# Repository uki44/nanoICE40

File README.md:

# nanoICE40
custom fpga development board using the ice40 fpga from lattice

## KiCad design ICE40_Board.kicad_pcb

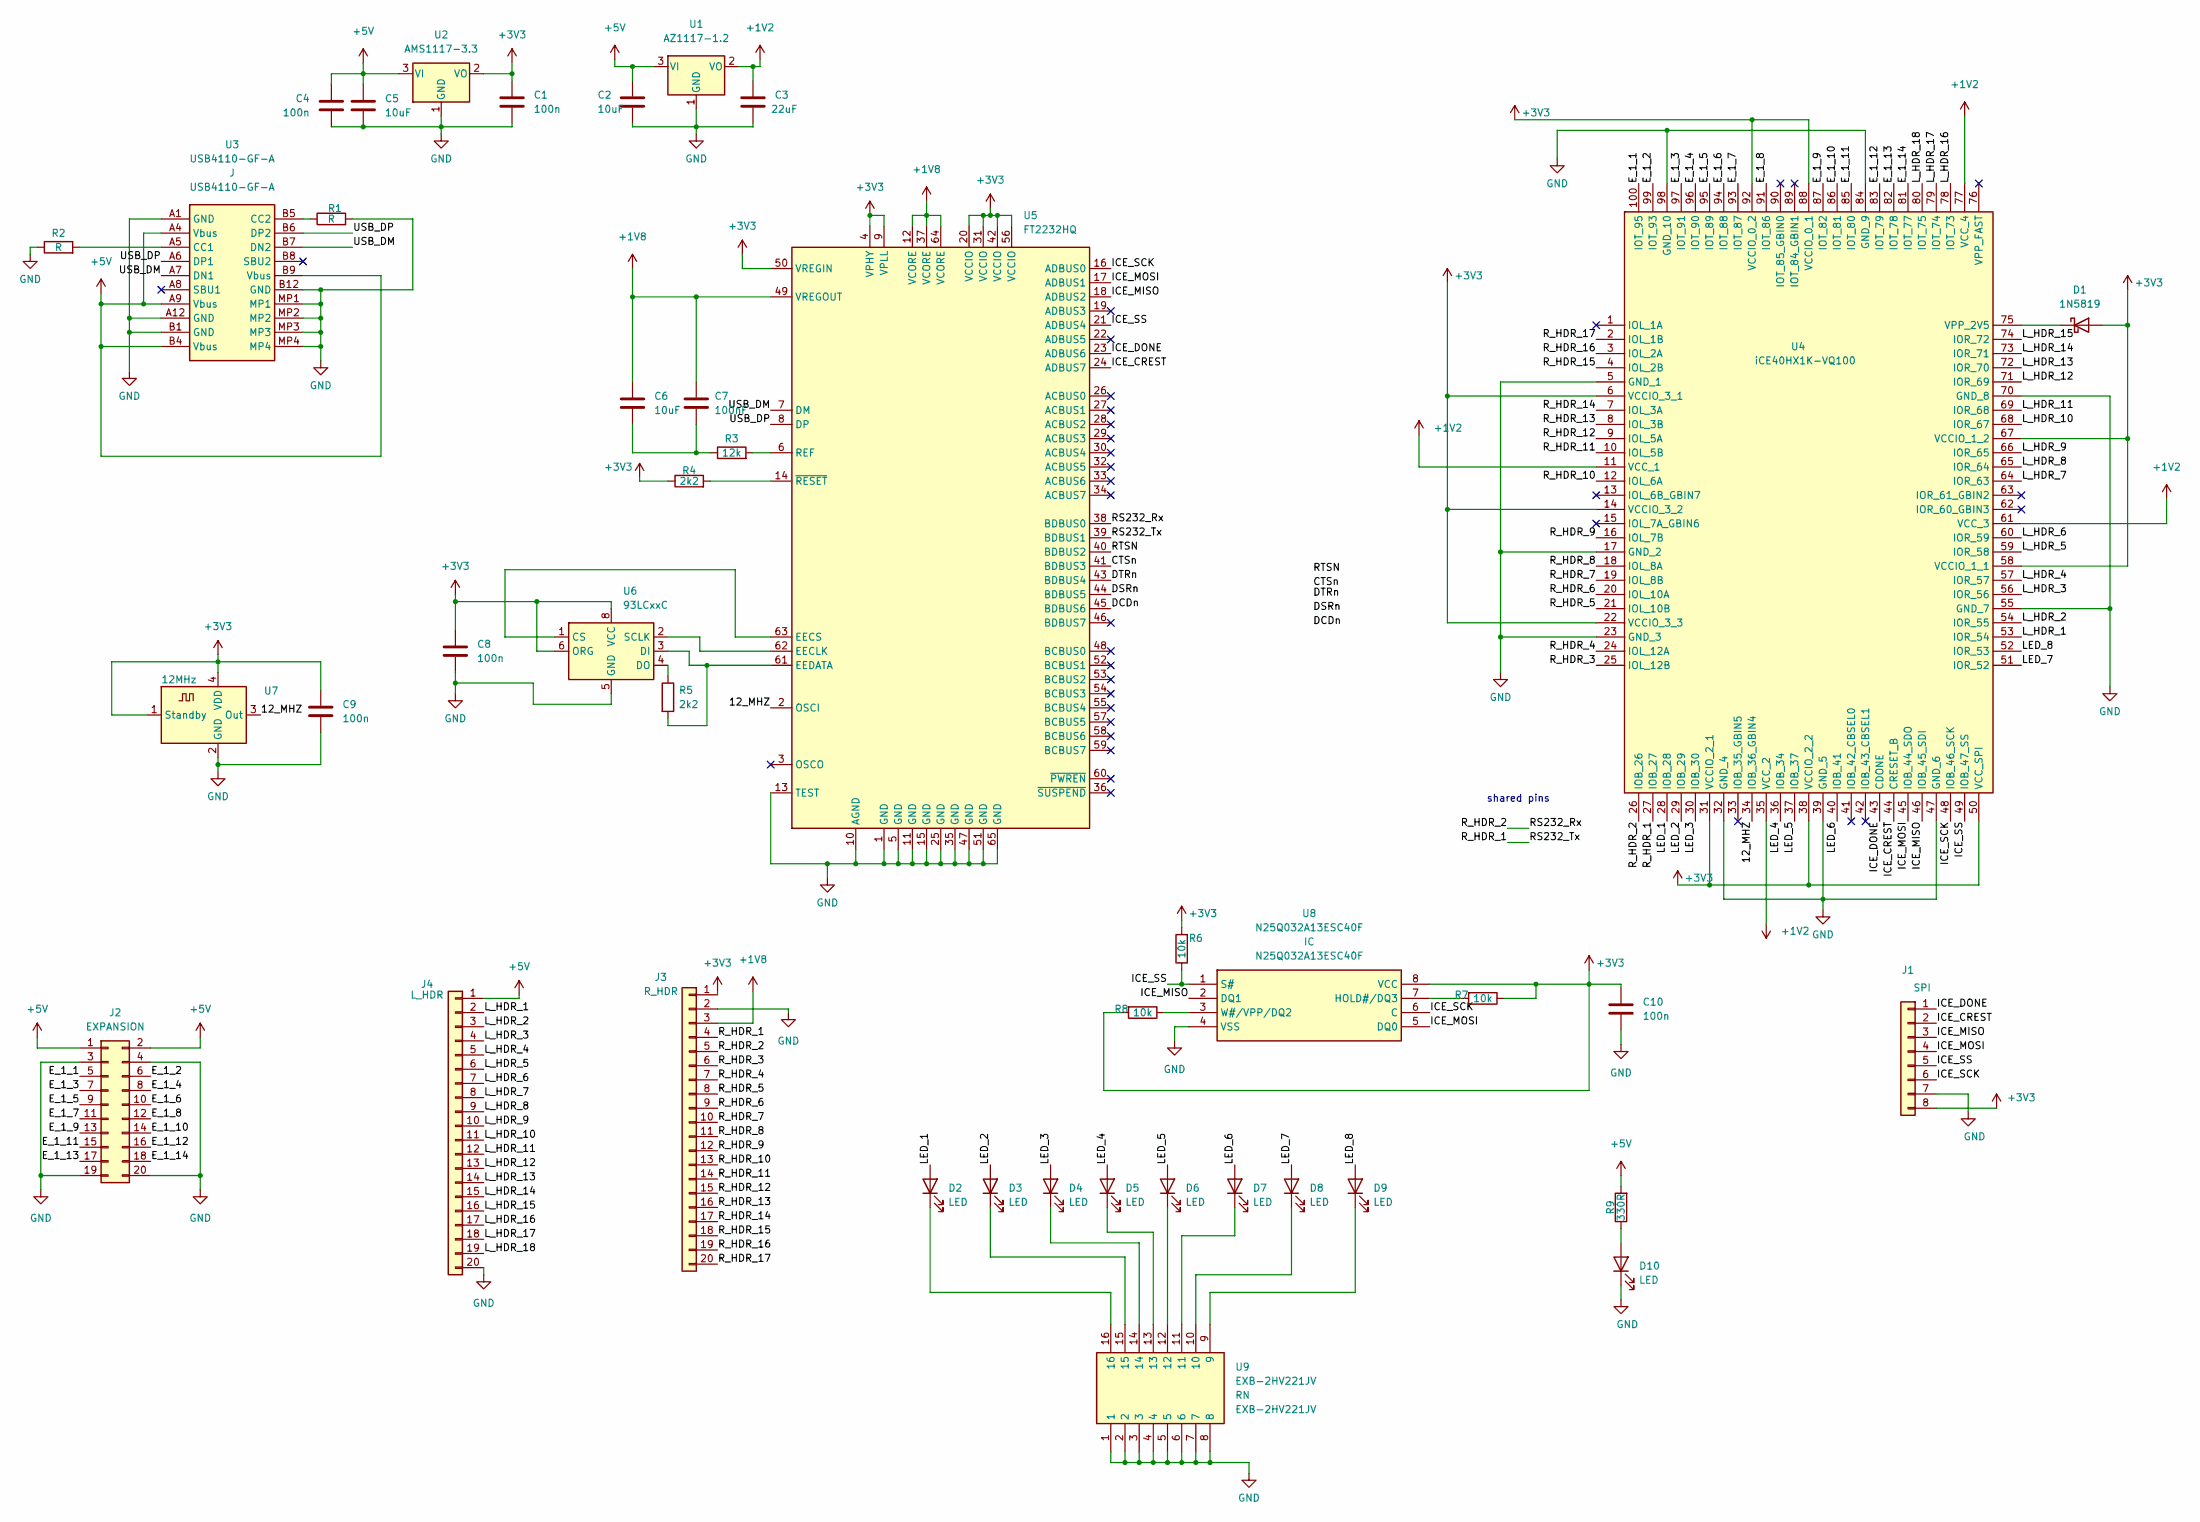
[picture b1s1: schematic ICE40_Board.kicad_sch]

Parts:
C1, C4, C8, C9, C10: 100n; C_0603_1608Metric
C2, C5, C6: 10uF; C_0603_1608Metric
C3: 22uF; C_0603_1608Metric
C7: 100nF; C_0603_1608Metric
D1: 1N5819; D_SOD-123
D2, D3, D4, D5, D6, D7, D8, D9, D10: LED; LED_0603_1608Metric
J1: SPI; PinHeader_1x08_P1.27mm_Vertical
J2: EXPANSION; PinHeader_2x10_P2.54mm_Vertical
J3: R_HDR; PinHeader_1x20_P2.54mm_Vertical
J4: L_HDR; PinHeader_1x20_P2.54mm_Vertical
R1, R2: R; R_0603_1608Metric
R3: 12k; R_0603_1608Metric
R4, R5: 2k2; R_0603_1608Metric
R6, R7, R8: 10k; R_0603_1608Metric
R9: 330R; R_0603_1608Metric
U1: AZ1117-1.2; SOT-223
U2: AMS1117-3.3; SOT-223
U3: USB4110-GF-A; USB4110GFA; Mouser Part Number 640-USB4110-GF-A
U4: iCE40HX1K-VQ100; QFP50P1600X1600X120-100N; Mouser Part Number 842-ICE40HX1K-VQ100
U5: FT2232HQ; QFN-64-1EP_9x9mm_P0.5mm_EP4.35x4.35mm
U6: 93LCxxC; SOIC127P600X175-8N
U7: 12MHz; Oscillator_SMD_Abracon_ASDMB-4Pin_2.5x2.0mm
U8: N25Q032A13ESC40F; SOIC127P600X175-8N; Mouser Part Number 913-N25Q032A13ESC40F
U9: EXB-2HV221JV; EXB2HV221JV; Mouser Part Number 667-EXB-2HV221JV

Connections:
+1V2: C3.1, U1.2 (VO), U4.11 (VCC_1), U4.35 (VCC_2), U4.61 (VCC_3), U4.77 (VCC_4)
+1V8: C6.1, C7.1, J3.3, U5.12 (VCORE), U5.37 (VCORE), U5.49 (VREGOUT), U5.64 (VCORE)
+3V3: C1.1, C8.1, C9.1, C10.1, D1.2 (A), J1.8, J3.1, R4.1, R6.2, R7.1, R8.2, U2.2 (VO), U4.6 (VCCIO_3_1), U4.14 (VCCIO_3_2), U4.22 (VCCIO_3_3), U4.31 (VCCIO_2_1), U4.38 (VCCIO_2_2), U4.50 (VCC_SPI), U4.58 (VCCIO_1_1), U4.67 (VCCIO_1_2), U4.88 (VCCIO_0_1), U4.92 (VCCIO_0_2), U5.4 (VPHY), U5.9 (VPLL), U5.20 (VCCIO), U5.31 (VCCIO), U5.42 (VCCIO), U5.50 (VREGIN), U5.56 (VCCIO), U6.6 (ORG), U6.8 (VCC), U7.1 (Standby), U7.4 (VDD), U8.8 (VCC)
+5V: C2.1, C4.2, C5.1, J2.1, J2.2, J4.1, R9.2, U1.3 (VI), U2.3 (VI), U3.A4 (Vbus), U3.A9 (Vbus), U3.B4 (Vbus), U3.B9 (Vbus)
/12_MHZ: U4.34 (IOB_36_GBIN4), U5.2 (OSCI), U7.3 (Out)
/CTSn: U5.41 (BDBUS3)
/DCDn: U5.45 (BDBUS6)
/DSRn: U5.44 (BDBUS5)
/DTRn: U5.43 (BDBUS4)
/E_1_1: J2.5, U4.100 (IOT_95)
/E_1_2: J2.6, U4.99 (IOT_93)
/E_1_3: J2.7, U4.97 (IOT_91)
/E_1_4: J2.8, U4.96 (IOT_90)
/E_1_5: J2.9, U4.95 (IOT_89)
/E_1_6: J2.10, U4.94 (IOT_88)
/E_1_7: J2.11, U4.93 (IOT_87)
/E_1_8: J2.12, U4.91 (IOT_86)
/E_1_9: J2.13, U4.87 (IOT_82)
/E_1_10: J2.14, U4.86 (IOT_81)
/E_1_11: J2.15, U4.85 (IOT_80)
/E_1_12: J2.16, U4.83 (IOT_79)
/E_1_13: J2.17, U4.82 (IOT_78)
/E_1_14: J2.18, U4.81 (IOT_77)
/ICE_CREST: J1.2, U4.44 (CRESET_B), U5.24 (ADBUS7)
/ICE_DONE: J1.1, U4.43 (CDONE), U5.23 (ADBUS6)
/ICE_MISO: J1.3, U4.46 (IOB_45_SDI), U5.18 (ADBUS2), U8.2 (DQ1)
/ICE_MOSI: J1.4, U4.45 (IOB_44_SDO), U5.17 (ADBUS1), U8.5 (DQ0)
/ICE_SCK: J1.6, U4.48 (IOB_46_SCK), U5.16 (ADBUS0), U8.6 (C)
/ICE_SS: J1.5, R6.1, U4.49 (IOB_47_SS), U5.21 (ADBUS4), U8.1 (S#)
/LED_1: D2.2 (A), U4.28 (IOB_28)
/LED_2: D3.2 (A), U4.29 (IOB_29)
/LED_3: D4.2 (A), U4.30 (IOB_30)
/LED_4: D5.2 (A), U4.36 (IOB_34)
/LED_5: D6.2 (A), U4.37 (IOB_37)
/LED_6: D7.2 (A), U4.40 (IOB_41)
/LED_7: D8.2 (A), U4.51 (IOR_52)
/LED_8: D9.2 (A), U4.52 (IOR_53)
/L_HDR_1: J4.2, U4.53 (IOR_54)
/L_HDR_2: J4.3, U4.54 (IOR_55)
/L_HDR_3: J4.4, U4.56 (IOR_56)
/L_HDR_4: J4.5, U4.57 (IOR_57)
/L_HDR_5: J4.6, U4.59 (IOR_58)
/L_HDR_6: J4.7, U4.60 (IOR_59)
/L_HDR_7: J4.8, U4.64 (IOR_63)
/L_HDR_8: J4.9, U4.65 (IOR_64)
/L_HDR_9: J4.10, U4.66 (IOR_65)
/L_HDR_10: J4.11, U4.68 (IOR_67)
/L_HDR_11: J4.12, U4.69 (IOR_68)
/L_HDR_12: J4.13, U4.71 (IOR_69)
/L_HDR_13: J4.14, U4.72 (IOR_70)
/L_HDR_14: J4.15, U4.73 (IOR_71)
/L_HDR_15: J4.16, U4.74 (IOR_72)
/L_HDR_16: J4.17, U4.78 (IOT_73)
/L_HDR_17: J4.18, U4.79 (IOT_74)
/L_HDR_18: J4.19, U4.80 (IOT_75)
/RS232_Rx: J3.5, U4.26 (IOB_26), U5.38 (BDBUS0)
/RS232_Tx: J3.4, U4.27 (IOB_27), U5.39 (BDBUS1)
/RTSN: U5.40 (BDBUS2)
/R_HDR_3: J3.6, U4.25 (IOL_12B)
/R_HDR_4: J3.7, U4.24 (IOL_12A)
/R_HDR_5: J3.8, U4.21 (IOL_10B)
/R_HDR_6: J3.9, U4.20 (IOL_10A)
/R_HDR_7: J3.10, U4.19 (IOL_8B)
/R_HDR_8: J3.11, U4.18 (IOL_8A)
/R_HDR_9: J3.12, U4.16 (IOL_7B)
/R_HDR_10: J3.13, U4.12 (IOL_6A)
/R_HDR_11: J3.14, U4.10 (IOL_5B)
/R_HDR_12: J3.15, U4.9 (IOL_5A)
/R_HDR_13: J3.16, U4.8 (IOL_3B)
/R_HDR_14: J3.17, U4.7 (IOL_3A)
/R_HDR_15: J3.18, U4.4 (IOL_2B)
/R_HDR_16: J3.19, U4.3 (IOL_2A)
/R_HDR_17: J3.20, U4.2 (IOL_1B)
/USB_DM: U3.A7 (DN1), U3.B7 (DN2), U5.7 (DM)
/USB_DP: U3.A6 (DP1), U3.B6 (DP2), U5.8 (DP)
GND: C1.2, C2.2, C3.2, C4.1, C5.2, C8.2, C9.2, C10.2, D10.1 (K), J1.7, J2.3, J2.4, J2.19, J2.20, J3.2, J4.20, R1.2, R2.1, U1.1 (GND), U2.1 (GND), U3.A1 (GND), U3.A12 (GND), U3.B1 (GND), U3.B12 (GND), U3.MP1, U3.MP2, U3.MP3, U3.MP4, U4.5 (GND_1), U4.17 (GND_2), U4.23 (GND_3), U4.32 (GND_4), U4.39 (GND_5), U4.47 (GND_6), U4.55 (GND_7), U4.70 (GND_8), U4.84 (GND_9), U4.98 (GND_10), U5.1 (GND), U5.5 (GND), U5.10 (AGND), U5.11 (GND), U5.13 (TEST), U5.15 (GND), U5.25 (GND), U5.35 (GND), U5.47 (GND), U5.51 (GND), U5.65 (GND), U6.5 (GND), U7.2 (GND), U8.4 (VSS), U9.1, U9.2, U9.3, U9.4, U9.5, U9.6, U9.7, U9.8
unnamed: C6.2, C7.2, R3.1
unnamed: D1.1 (K), U4.75 (VPP_2V5)
unnamed: D2.1 (K), U9.16
unnamed: D3.1 (K), U9.15
unnamed: D4.1 (K), U9.14
unnamed: D5.1 (K), U9.13
unnamed: D6.1 (K), U9.12
unnamed: D7.1 (K), U9.11
unnamed: D8.1 (K), U9.10
unnamed: D9.1 (K), U9.9
unnamed: D10.2 (A), R9.1
unnamed: R1.1, U3.B5 (CC2)
unnamed: R2.2, U3.A5 (CC1)
unnamed: R3.2, U5.6 (REF)
unnamed: R4.2, U5.14 (~RESET)
unnamed: R5.1, U6.4 (DO)
unnamed: R5.2, U5.61 (EEDATA), U6.3 (DI)
unnamed: R7.2, U8.7 (HOLD#/DQ3)
unnamed: R8.1, U8.3 (W#/VPP/DQ2)
unnamed: U5.62 (EECLK), U6.2 (SCLK)
unnamed: U5.63 (EECS), U6.1 (CS)

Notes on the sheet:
shared pins

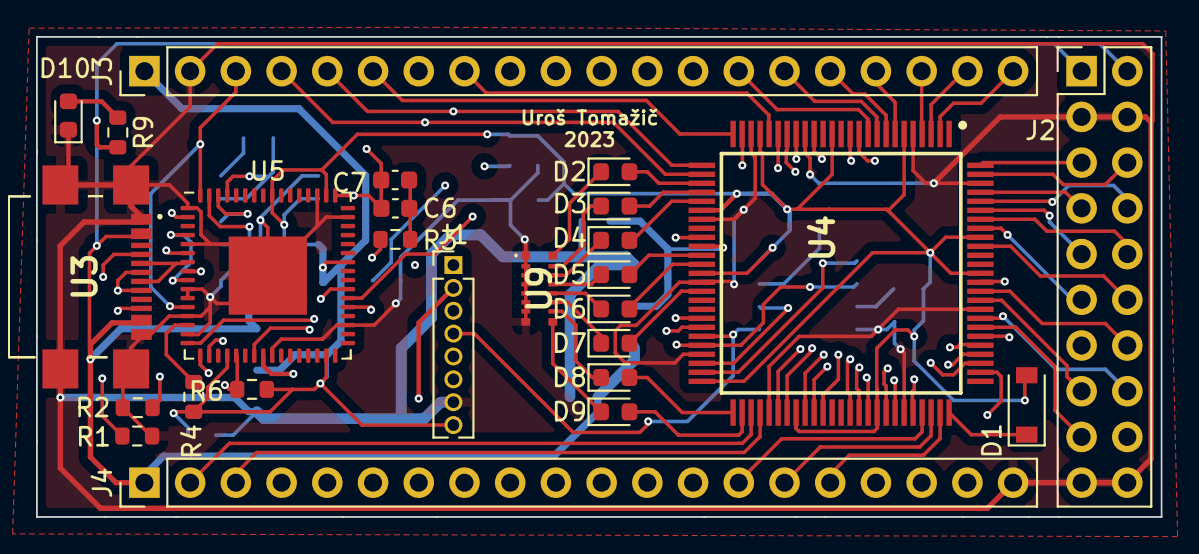
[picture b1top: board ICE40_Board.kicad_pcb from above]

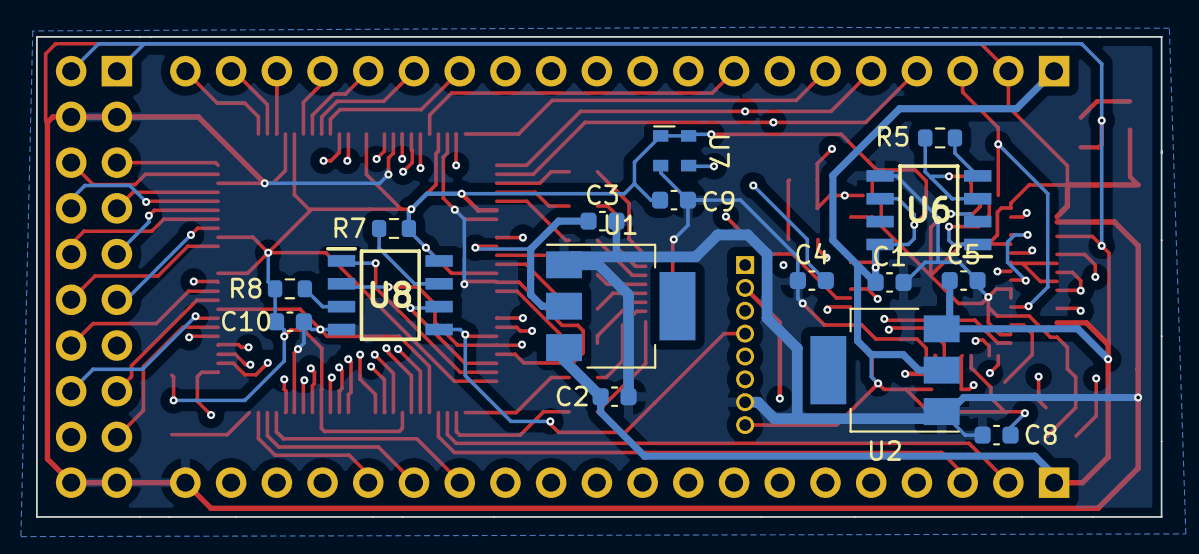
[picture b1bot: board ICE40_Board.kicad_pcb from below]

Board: 4 copper layers, 62.5 x 26.7 mm, 42 parts (16 on the bottom side), 92 nets.

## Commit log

2023-10-06 added power led
2023-10-06 added led
2023-11-13 added example
